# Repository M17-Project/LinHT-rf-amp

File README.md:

[![CC BY-NC-SA 4.0][cc-by-nc-sa-shield]][cc-by-nc-sa]

# LinHT-rf-amp

Standalone RF power amplifier module for the LinHT handheld, built around the **Guerrilla RF GRF5604**.  
This repository houses a proof-of-concept (PoC) board used to evaluate matching, biasing, efficiency, and linearity in the **420–450 MHz** band. Results from this effort will feed back into, and eventually be integrated with the
[main LinHT hardware project](https://github.com/M17-Project/LinHT-hw).

> Goal: validate a practical PA chain for LinHT. Once the approach is proven, the PA will be integrated into LinHT to enable higher output power (targeting ≈ 5 W at the radio level). This board is for laboratory development and characterization.

## Status

- **Design tested - works.**
- Tuning follows the vendor's reference design for **397–470 MHz**

## Safety & Compliance

This hardware is intended for **licensed amateur radio** experimentation. Users are responsible for ensuring compliance with local regulations (spectral masks, occupied bandwidth, power limits, spurious emissions) before on-air use.

## License

This work is licensed under a  
[Creative Commons Attribution-NonCommercial-ShareAlike 4.0 International License][cc-by-nc-sa].

[![CC BY-NC-SA 4.0][cc-by-nc-sa-image]][cc-by-nc-sa]

[cc-by-nc-sa]: http://creativecommons.org/licenses/by-nc-sa/4.0/
[cc-by-nc-sa-image]: https://licensebuttons.net/l/by-nc-sa/4.0/88x31.png
[cc-by-nc-sa-shield]: https://img.shields.io/badge/License-CC%20BY--NC--SA%204.0-lightgrey.svg

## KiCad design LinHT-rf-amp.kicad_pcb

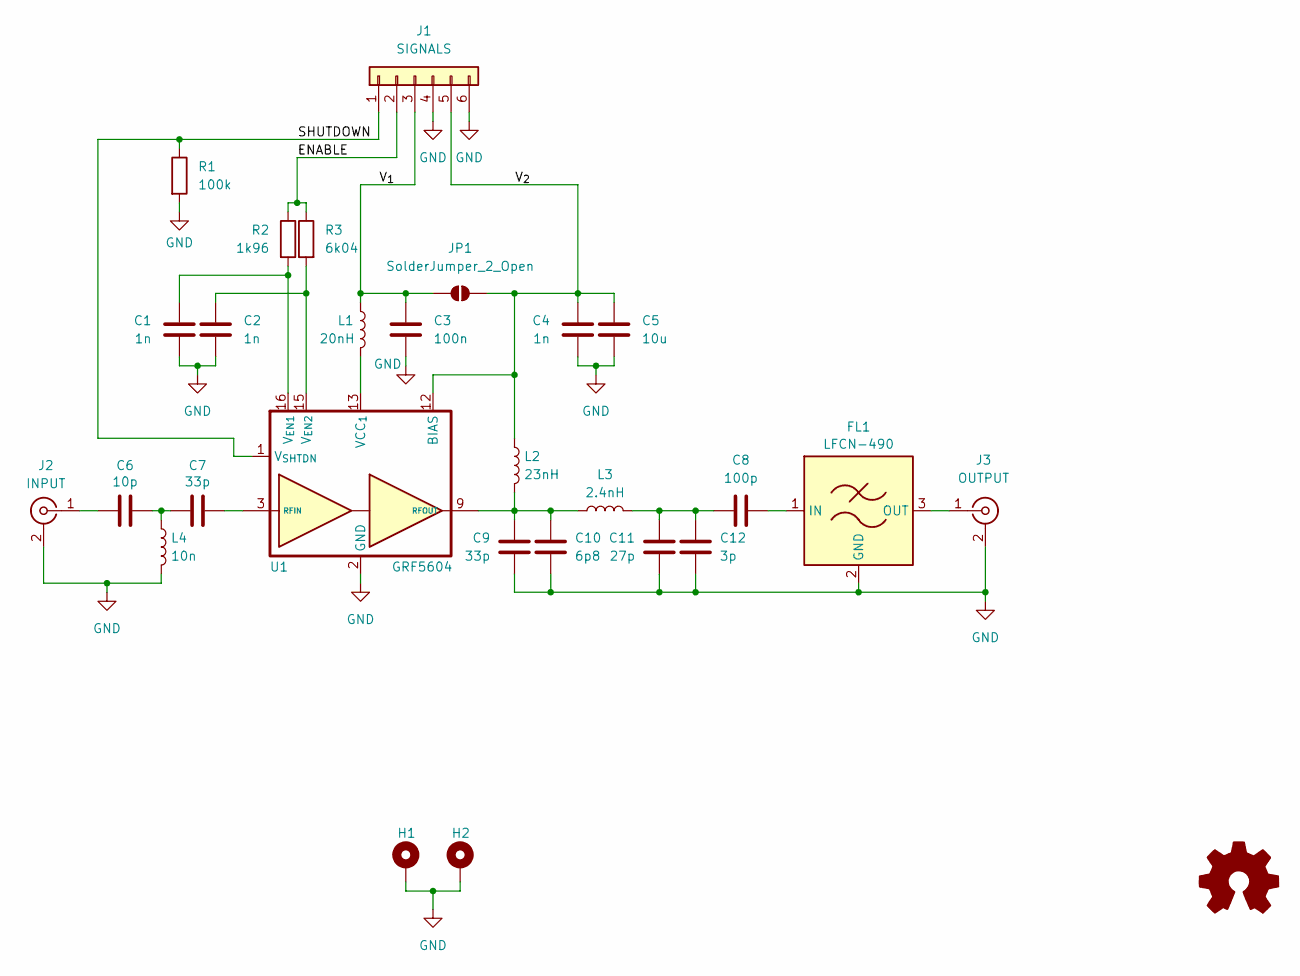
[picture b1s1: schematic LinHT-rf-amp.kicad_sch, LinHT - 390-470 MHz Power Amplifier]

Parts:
C1, C2, C4: 1n; C_0402_1005Metric; LCSC C161523
C3: 100n; C_0402_1005Metric; LCSC C913614
C5: 10u; C_0402_1005Metric; LCSC C237279
C6: 10p; C_0402_1005Metric; LCSC C782046
C7, C9: 33p; C_0402_1005Metric; LCSC C464434
C8: 100p; C_0402_1005Metric; LCSC C77177
C10: 6p8; C_0402_1005Metric; LCSC C88896
C11: 27p; C_0402_1005Metric; LCSC C88883
C12: 3p; C_0402_1005Metric; LCSC C88891
FL1: LFCN-490; Filter_Mini-Circuits_FV1206; LCSC C3008205
H1, H2: MountingHole_Pad_MP; MountingHole_2.2mm_M2_DIN965_Pad
J1: SIGNALS; PinHeader_1x06_P2.54mm_Vertical
J2: INPUT; SMA_Amphenol_132289_EdgeMount
J3: OUTPUT; SMA_Amphenol_132289_EdgeMount
JP1: SolderJumper_2_Open; SolderJumper-2_P1.3mm_Open_RoundedPad1.0x1.5mm
L1: 20nH; L_0402_1005Metric; LCSC C20623501
L2: 23nH; 0908SQ-23N; LCSC C42418190
L3: 2.4nH; L_0603_1608Metric; LCSC C2042508
L4: 10n; L_0402_1005Metric; LCSC C668375
R1: 100k; R_0402_1005Metric; LCSC C25741
R2: 1k96; R_0402_1005Metric; LCSC C70427
R3: 6k04; R_0402_1005Metric; LCSC C25913
SYM1: Logo_Open_Hardware_Small; OSHW-Logo2_7.3x6mm_SilkScreen
U1: GRF5604; QFN-16-1EP_3x3mm_P0.5mm_EP1.7x1.7mm_ThermalVias

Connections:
/ENABLE: J1.2, R2.1, R3.1
/SHUTDOWN: J1.1, R1.1, U1.1 (V_{SHTDN})
/V_{1}: C3.2, J1.3, JP1.1 (A), L1.1
/V_{2}: C4.2, C5.2, J1.5, JP1.2 (B), L2.1, U1.12 (BIAS)
GND: C1.2, C2.2, C3.1, C4.1, C5.1, C9.1, C10.1, C11.1, C12.1, FL1.2 (GND), FL1.4 (GND), H1.1, H2.1, J1.4, J1.6, J2.2 (Ext), J3.2 (Ext), L4.2, R1.2, U1.2 (GND), U1.5 (GND), U1.6 (GND), U1.7 (GND), U1.8 (GND), U1.11 (GND), U1.14 (GND), U1.17 (GND)
unnamed: C6.2, C7.1, L4.1
unnamed: C7.2, U1.3 (RFIN), U1.4 (RFIN)
unnamed: C9.2, C10.2, L2.2, L3.1, U1.9 (RFOUT), U1.10 (RFOUT)
unnamed: C8.1, C11.2, C12.2, L3.2
unnamed: C8.2, FL1.1 (IN)
unnamed: FL1.3 (OUT), J3.1 (In)
unnamed: C6.1, J2.1 (In)
unnamed: L1.2, U1.13 (VCC_{1})
unnamed: C1.1, R2.2, U1.16 (V_{EN1})
unnamed: C2.1, R3.2, U1.15 (V_{EN2})

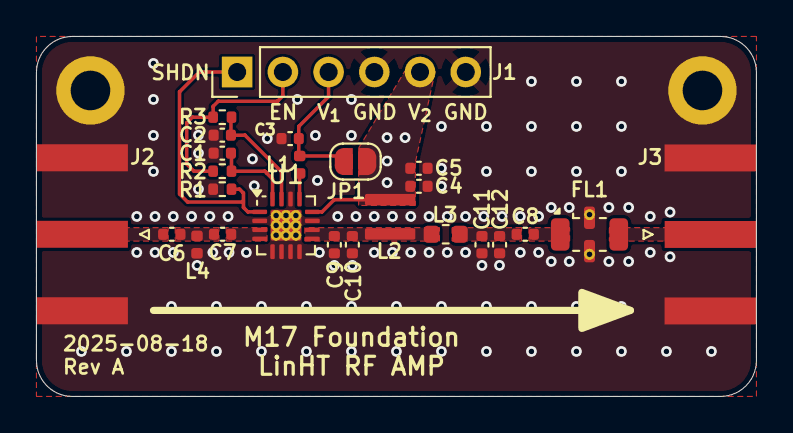
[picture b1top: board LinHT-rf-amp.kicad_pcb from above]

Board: 4 copper layers, 40.0 x 20.0 mm, 27 parts (0 on the bottom side), 15 nets.

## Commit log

2025-08-17 Added a basic schematics (using KiCAD 9.0)
2025-08-18 Fixed GRF5604 symbol
2025-08-18 Added component values and connectors
2025-08-19 Modified the GRF5604 symbol
2025-08-19 Added footprint and 3D model for the 23nH Coilcraft coil
2025-08-19 Added LCSC and manufacturer numbers for all components
2025-08-19 Added signal names to the schematics
2025-08-19 Finished basic layout
    * 4 layer board
    * Dimensions 35x20 mm
2025-08-19 Added basic Github Actions workflow
2025-08-19 Fixed RF traces, reset annotation, added M2 holes
2025-08-19 Added more vias and via fencing around RF traces
2025-08-19 Changed "copper edge clearance" to warning only
2025-08-20 Modified "copper to edge" clearance from 0.5 to 0.3 mm
    Tjis value is b ased on the PCBway recommendation.
2025-08-20 Excluded J1-J3 from position files
2025-08-20 Added a low pass filter LFCN-490+
2025-08-20 Updated layout with the low pass filter
    Board dimensions has to be increased to 40x20 mm (original 35x20mm)
2025-08-25 Changed footprint of the GRF5604 to the QFN-16 with 9 vias
    Default KiCAD footprint for QFN-16-1EP_3x3mm_P0.5mm_EP1.7x1.7_ThermalVias
    has only four 0.2 mm vias in the GND pad corners. This is not enough
    to transfer the heat.
    This commit modifies the default footprint to have 9 vias of 0.3 mm.
2025-08-25 Updated design to use new GRF5604 footprint
2025-08-25 Fixed shape of the V2 signal polygon on the top layer
2025-08-25 Remove alternative part number for the L2 coil
    Original Coilcraft coil 0908SQ-23NJLC is not easily available at LCSC,
    so we chose the alternative part XR0908SQ-23NJLC with the same params.
2025-08-26 Fixed position of the bottom silkscreen text
2025-08-26 silkscreen update
    frequency range starts at 397 MHz
2025-08-26 title update
    frequency range starts at 397 MHz
2025-08-26 ignore .zip files
2026-05-29 Update README.md
    amplifier works
